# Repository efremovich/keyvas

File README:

Клавиатура для Василисы

https://monacokeys.de/en/products/niuniu-40-40-low-profile-mechanical-keyboard-kit

Плагин для генерации 
https://github.com/adamws/kicad-kbplacer

KLE 

kle.klava.org

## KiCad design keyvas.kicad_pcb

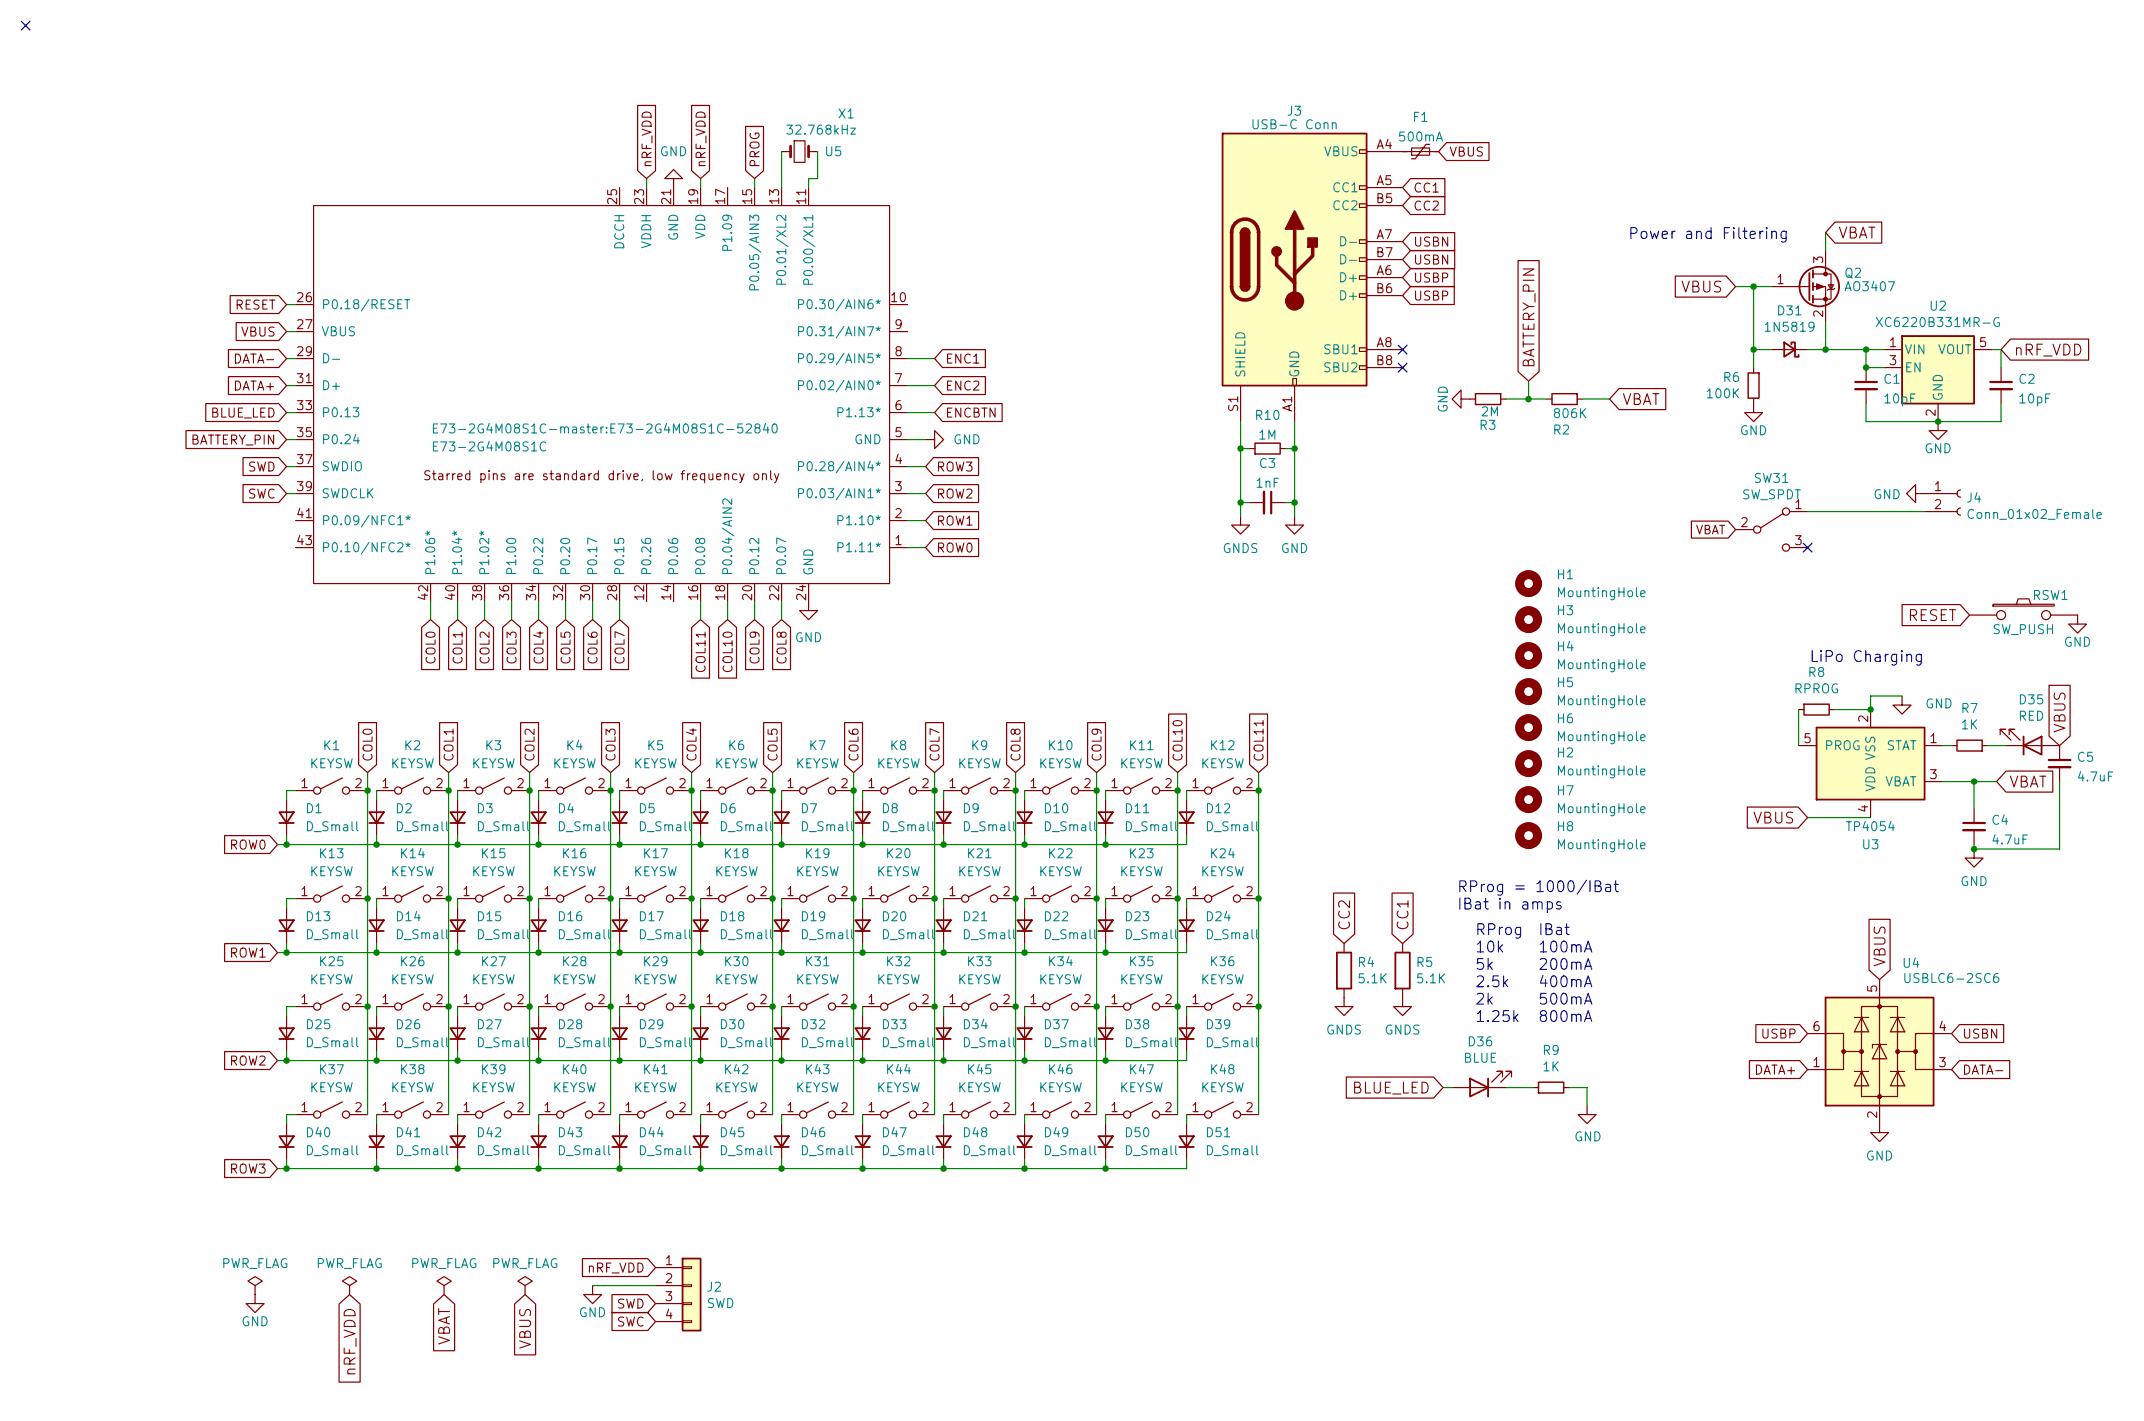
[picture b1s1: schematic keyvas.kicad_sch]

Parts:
C1, C2: 10pF; C_0603_1608Metric_REV; LCSC C1634
C3: 1nF; C_0603_1608Metric_REV; LCSC C1588
C4, C5: 4.7uF; C_0603_1608Metric_REV; LCSC C19666
D1, D2, D3, D4, D5, D6, D7, D8, D9, D10, D11, D12, D13, D14, D15, D16, D17, D18, D19, D20, D21, D22, D23, D24, D25, D26, D27, D28, D29, D30, D32, D33, D34, D37, D38, D39, D40, D41, D42, D43, D44, D45, D46, D47, D48, D49, D50, D51: D_Small; D3_SMD
D31: 1N5819; D_SOD-323_HandSoldering_REV
D35: RED; LED_0603_1608Metric_REV
D36: BLUE; LED_0603_1608Metric_REV
F1: 500mA; Fuse_1206_3216Metric_REV; LCSC C883122
H1, H2, H3, H4, H5, H6, H7, H8: MountingHole; Hole 3,2
J2: SWD; connector_swd_REV
J3: USB-C Conn; TYPE-C-31-M-13C
J4: Conn_01x02_Female; Battery_TH
K1, K2, K3, K4, K5, K6, K7, K8, K9, K10, K11, K12, K13, K14, K15, K16, K17, K18, K19, K20, K21, K22, K23, K24, K25, K26, K27, K28, K29, K30, K31, K32, K33, K34, K35, K36, K37, K38, K39, K40, K41, K42, K43, K44, K45, K46, K47, K48: KEYSW; SW_Gateron_LowProfile_THT
Q2: AO3407; SOT-23_Handsoldering_REV
R2: 806K; R_0603_1608Metric_REV
R3: 2M; R_0603_1608Metric_REV
R4, R5: 5.1K; R_0603_1608Metric_REV
R6: 100K; R_0603_1608Metric_REV
R7, R9: 1K; R_0603_1608Metric_REV
R8: RPROG; R_0603_1608Metric_REV
R10: 1M; R_0603_1608Metric_REV; LCSC C22935
RSW1: SW_PUSH; SW_SPST_EVQP7C_REV
SW31: SW_SPDT; SW_SPDT+H-MSK12C01_hor(7pin_SMD)_REV
U2: XC6220B331MR-G; SOT-23-5_HandSoldering_REV
U3: TP4054; SOT-23-5_HandSoldering_REV
U4: USBLC6-2SC6; SOT-23-6_Handsoldering_REV; LCSC C558442
U5: E73-2G4M08S1C; E73-2G4M08S1C-52840
X1: 32.768kHz; Crystal_SMD_MicroCrystal_CM9V-T1A-2Pin_1.6x1.0mm_HandSolder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

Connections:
BATTERY_PIN: R2.2, R3.1, U5.35 (P0.24)
BLUE_LED: D36.2 (A), U5.33 (P0.13)
CC1: J3.A5 (CC1), R5.1
CC2: J3.B5 (CC2), R4.1
COL0: K1.2 (B), K13.2 (B), K25.2 (B), K37.2 (B), U5.42 (P1.06*)
COL1: K2.2 (B), K14.2 (B), K26.2 (B), K38.2 (B), U5.40 (P1.04*)
COL2: K3.2 (B), K15.2 (B), K27.2 (B), K39.2 (B), U5.38 (P1.02*)
COL3: K4.2 (B), K16.2 (B), K28.2 (B), K40.2 (B), U5.36 (P1.00)
COL4: K5.2 (B), K17.2 (B), K29.2 (B), K41.2 (B), U5.34 (P0.22)
COL5: K6.2 (B), K18.2 (B), K30.2 (B), K42.2 (B), U5.32 (P0.20)
COL6: K7.2 (B), K19.2 (B), K31.2 (B), K43.2 (B), U5.30 (P0.17)
COL7: K8.2 (B), K20.2 (B), K32.2 (B), K44.2 (B), U5.28 (P0.15)
COL8: K9.2 (B), K21.2 (B), K33.2 (B), K45.2 (B), U5.22 (P0.07)
COL9: K10.2 (B), K22.2 (B), K34.2 (B), K46.2 (B), U5.20 (P0.12)
COL10: K11.2 (B), K23.2 (B), K35.2 (B), K47.2 (B), U5.18 (P0.04/AIN2)
COL11: K12.2 (B), K24.2 (B), K36.2 (B), K48.2 (B), U5.16 (P0.08)
DATA+: U4.1 (I/O1), U5.31 (D+)
DATA-: U4.3 (I/O2), U5.29 (D-)
ENC1: U5.8 (P0.29/AIN5*)
ENC2: U5.7 (P0.02/AIN0*)
ENCBTN: U5.6 (P1.13*)
GND: C1.2, C2.2, C3.1, C4.2, C5.2, J2.2, J3.A1 (GND), J3.A12 (GND), J3.B1 (GND), J3.B12 (GND), J4.1, R3.2, R6.2, R8.2, R9.2, R10.2, RSW1.2, U2.2 (GND), U3.2 (VSS), U4.2 (GND), U5.5 (GND), U5.21 (GND), U5.24 (GND)
GNDS: C3.2, J3.S1 (SHIELD), R4.2, R5.2, R10.1
unnamed: D1.2 (A), K1.1 (A)
unnamed: D2.2 (A), K2.1 (A)
unnamed: D3.2 (A), K3.1 (A)
unnamed: D4.2 (A), K4.1 (A)
unnamed: D5.2 (A), K5.1 (A)
unnamed: D6.2 (A), K6.1 (A)
unnamed: D7.2 (A), K7.1 (A)
unnamed: D8.2 (A), K8.1 (A)
unnamed: D9.2 (A), K9.1 (A)
unnamed: D10.2 (A), K10.1 (A)
unnamed: D11.2 (A), K11.1 (A)
unnamed: D12.2 (A), K12.1 (A)
unnamed: D13.2 (A), K13.1 (A)
unnamed: D14.2 (A), K14.1 (A)
unnamed: D15.2 (A), K15.1 (A)
unnamed: D16.2 (A), K16.1 (A)
unnamed: D17.2 (A), K17.1 (A)
unnamed: D18.2 (A), K18.1 (A)
unnamed: D19.2 (A), K19.1 (A)
unnamed: D20.2 (A), K20.1 (A)
unnamed: D21.2 (A), K21.1 (A)
unnamed: D22.2 (A), K22.1 (A)
unnamed: D23.2 (A), K23.1 (A)
unnamed: D24.2 (A), K24.1 (A)
unnamed: D25.2 (A), K25.1 (A)
unnamed: D26.2 (A), K26.1 (A)
unnamed: D27.2 (A), K27.1 (A)
unnamed: D28.2 (A), K28.1 (A)
unnamed: D29.2 (A), K29.1 (A)
unnamed: D30.2 (A), K30.1 (A)
unnamed: C1.1, D31.1 (K), Q2.2 (S), U2.1 (VIN), U2.3 (EN)
unnamed: D32.2 (A), K31.1 (A)
unnamed: D33.2 (A), K32.1 (A)
unnamed: D34.2 (A), K33.1 (A)
unnamed: D35.1 (K), R7.1
unnamed: D36.1 (K), R9.1
unnamed: D37.2 (A), K34.1 (A)
unnamed: D38.2 (A), K35.1 (A)
unnamed: D39.2 (A), K36.1 (A)
unnamed: D40.2 (A), K37.1 (A)
unnamed: D41.2 (A), K38.1 (A)
unnamed: D42.2 (A), K39.1 (A)
unnamed: D43.2 (A), K40.1 (A)
unnamed: D44.2 (A), K41.1 (A)
unnamed: D45.2 (A), K42.1 (A)
unnamed: D46.2 (A), K43.1 (A)
unnamed: D47.2 (A), K44.1 (A)
unnamed: D48.2 (A), K45.1 (A)
unnamed: D49.2 (A), K46.1 (A)
unnamed: D50.2 (A), K47.1 (A)
unnamed: D51.2 (A), K48.1 (A)
unnamed: F1.1, J3.A4 (VBUS), J3.A9 (VBUS), J3.B4 (VBUS), J3.B9 (VBUS)
unnamed: J4.2, SW31.1 (A)
unnamed: R8.1, U3.5 (PROG)
unnamed: R7.2, U3.1 (STAT)
unnamed: U5.11 (P0.00/XL1), X1.2
unnamed: U5.13 (P0.01/XL2), X1.1
PROG: U5.15 (P0.05/AIN3)
RESET: RSW1.1, U5.26 (P0.18/RESET)
ROW0: D1.1 (K), D2.1 (K), D3.1 (K), D4.1 (K), D5.1 (K), D6.1 (K), D7.1 (K), D8.1 (K), D9.1 (K), D10.1 (K), D11.1 (K), D12.1 (K), U5.1 (P1.11*)
ROW1: D13.1 (K), D14.1 (K), D15.1 (K), D16.1 (K), D17.1 (K), D18.1 (K), D19.1 (K), D20.1 (K), D21.1 (K), D22.1 (K), D23.1 (K), D24.1 (K), U5.2 (P1.10*)
ROW2: D25.1 (K), D26.1 (K), D27.1 (K), D28.1 (K), D29.1 (K), D30.1 (K), D32.1 (K), D33.1 (K), D34.1 (K), D37.1 (K), D38.1 (K), D39.1 (K), U5.3 (P0.03/AIN1*)
ROW3: D40.1 (K), D41.1 (K), D42.1 (K), D43.1 (K), D44.1 (K), D45.1 (K), D46.1 (K), D47.1 (K), D48.1 (K), D49.1 (K), D50.1 (K), D51.1 (K), U5.4 (P0.28/AIN4*)
SWC: J2.4, U5.39 (SWDCLK)
SWD: J2.3, U5.37 (SWDIO)
USBN: J3.A7 (D-), J3.B7 (D-), U4.4 (I/O2)
USBP: J3.A6 (D+), J3.B6 (D+), U4.6 (I/O1)
VBAT: C4.1, Q2.3 (D), R2.1, SW31.2 (B), U3.3 (VBAT)
VBUS: C5.1, D31.2 (A), D35.2 (A), F1.2, Q2.1 (G), R6.1, U3.4 (VDD), U4.5 (VBUS), U5.27 (VBUS)
nRF_VDD: C2.1, J2.1, U2.5 (VOUT), U5.19 (VDD), U5.23 (VDDH)

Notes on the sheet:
RProg 10k 5k 2.5k 2k 1.25k
Power and Filtering
IBat 100mA 200mA 400mA 500mA 800mA
RProg = 1000/IBat IBat in amps
LiPo Charging

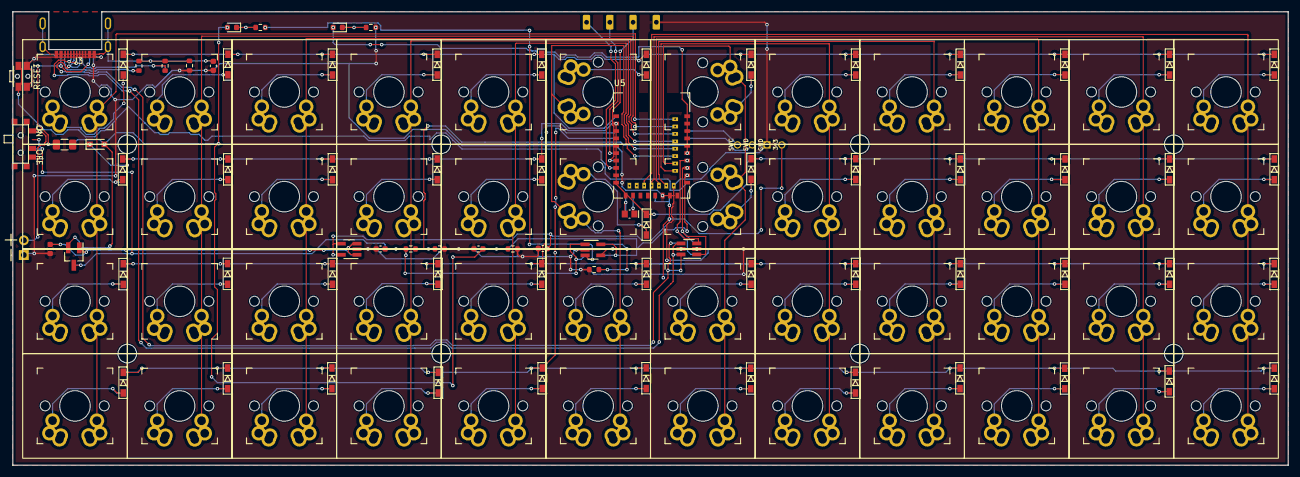
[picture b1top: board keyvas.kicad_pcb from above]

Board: 2 copper layers, 219.4 x 78.0 mm, 133 parts (0 on the bottom side), 89 nets.

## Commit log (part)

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2025-06-22 Init
2025-06-22 scheme
2025-06-23 Порядок в либах
2025-06-23 wip: настройка проекта
2025-06-29 Схема
2026-03-16 fix 2
2026-03-16 fix 3
2026-06-09 Продолжаем натягивать сову на глобус
2026-06-09 Продолжаем. Натянули. Расставляем
2026-06-10 Двигаем далее
2026-06-11 Двигаем далее 2
2026-06-12 Двигаем далее 3
2026-06-14 finish
2026-06-15 finish 2
